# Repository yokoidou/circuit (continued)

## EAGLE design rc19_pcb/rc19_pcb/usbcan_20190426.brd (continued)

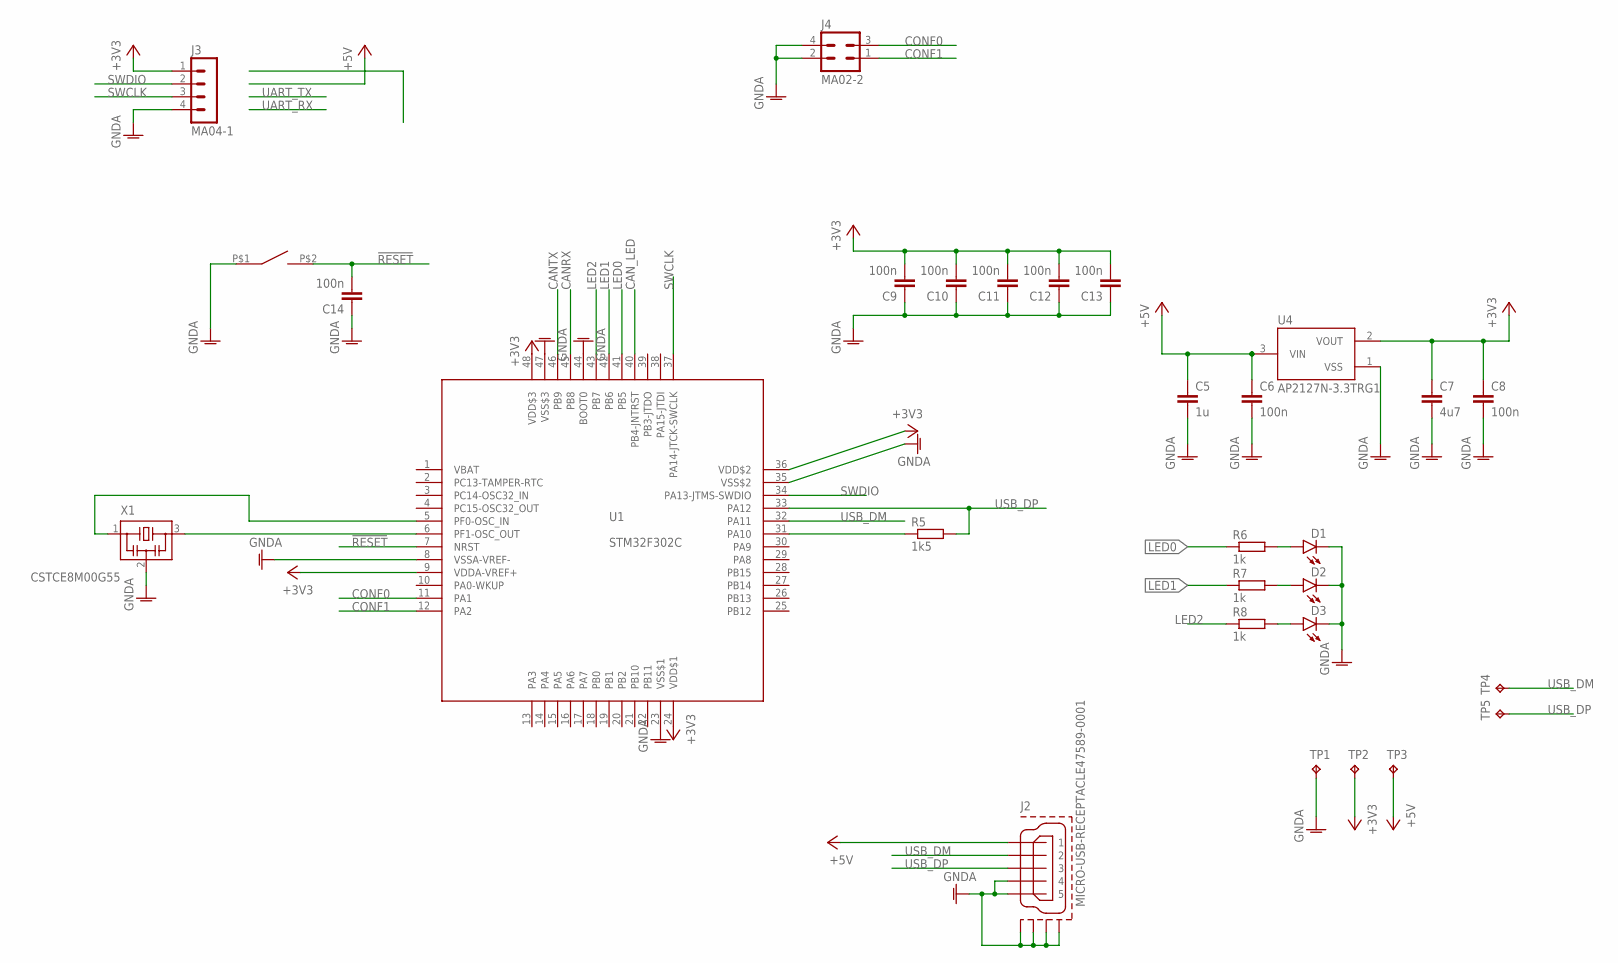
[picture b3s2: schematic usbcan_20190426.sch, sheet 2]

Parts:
C5: 1u; C0603
C6, C8, C9, C10, C11, C12, C13, C14: 100n; C0603
C7: 4u7; C0805
D1, D2, D3: LEDCHIPLED_0805; CHIPLED_0805
J2: MICRO-USB-RECEPTACLE47589-0001; 47589-0001
J3: MA04-1
J4: MA02-2; MA02-2W
R5: 1k5; R0603
R6, R7, R8: 1k; R0603
S1: SWITCH_TACTILETOP; SWITCH_TACTILE_3X6
TP1, TP2, TP3, TP4, TP5: TPB1,27; B1,27
U1: STM32F302C; LQFP48
U4: AP2127N-3.3TRG1; SOT95P240X110-3
X1: CSTCE8M00G55

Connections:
!RESET: C14.2, S1.P$2 (2), U1.7 (NRST)
+3V3: C7.1, C8.1, C9.2, C10.2, C11.2, C12.2, C13.2, J3.1, TP2.TP, U1.9 (VDDA-VREF+), U1.24 (VDD$1), U1.36 (VDD$2), U1.48 (VDD$3), U4.2 (VOUT); also elsewhere on the board
+5V: C5.1, C6.1, J2.1, TP3.TP, U4.3 (VIN)
CANRX: U1.45 (PB8); also elsewhere on the board
CANTX: U1.46 (PB9); also elsewhere on the board
CAN_LED: U1.40 (PB4-JNTRST); also elsewhere on the board
CONF0: J4.3, U1.11 (PA1)
CONF1: J4.1, U1.12 (PA2)
GNDA: C5.2, C6.2, C7.2, C8.2, C9.1, C10.1, C11.1, C12.1, C13.1, C14.1, D1.C, D2.C, D3.C, J2.4, J2.5, J2.CASING1 (GND1), J2.CASING2 (GND2), J2.CASING3 (GND3), J2.CASING4 (GND4), J2.P$1 (GND1), J2.P$2 (GND1), J2.P$3 (GND2), J2.P$4 (GND2), J3.4, J4.2, J4.4, S1.P$1 (1), TP1.TP, U1.8 (VSSA-VREF-), U1.23 (VSS$1), U1.35 (VSS$2), U1.44 (BOOT0), U1.47 (VSS$3), U4.1 (VSS), X1.2; also elsewhere on the board
LED0: R6.1, U1.41 (PB5)
LED1: R7.1, U1.42 (PB6)
LED2: R8.1, U1.43 (PB7)
unnamed: D2.A, R7.2
unnamed: D1.A, R6.2
unnamed: U1.6 (PF1-OSC_OUT), X1.3
unnamed: U1.5 (PF0-OSC_IN), X1.1
unnamed: R5.1, U1.31 (PA10)
unnamed: D3.A, R8.2
SWCLK: J3.3, U1.37 (PA14-JTCK-SWCLK)
SWDIO: J3.2, U1.34 (PA13-JTMS-SWDIO)
USB_DM: J2.2, TP4.TP, U1.32 (PA11)
USB_DP: J2.3, R5.2, TP5.TP, U1.33 (PA12)

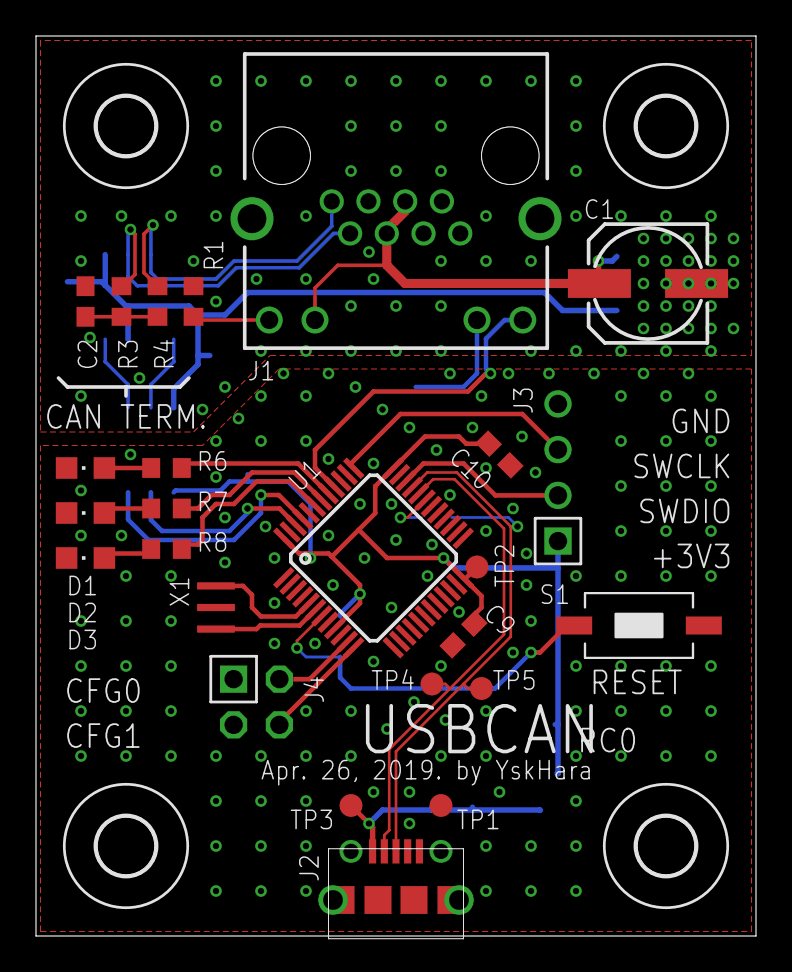
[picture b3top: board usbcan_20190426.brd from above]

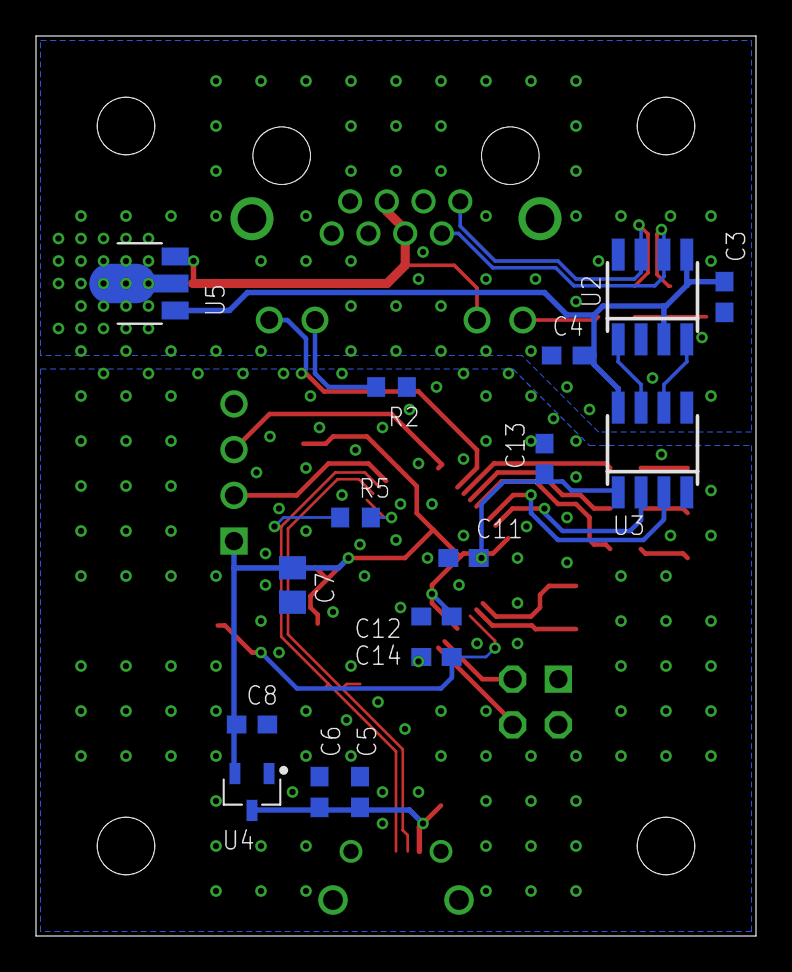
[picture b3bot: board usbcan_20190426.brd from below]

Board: 2 copper layers, 40.0 x 50.0 mm, 45 parts (16 on the bottom side), 32 nets.

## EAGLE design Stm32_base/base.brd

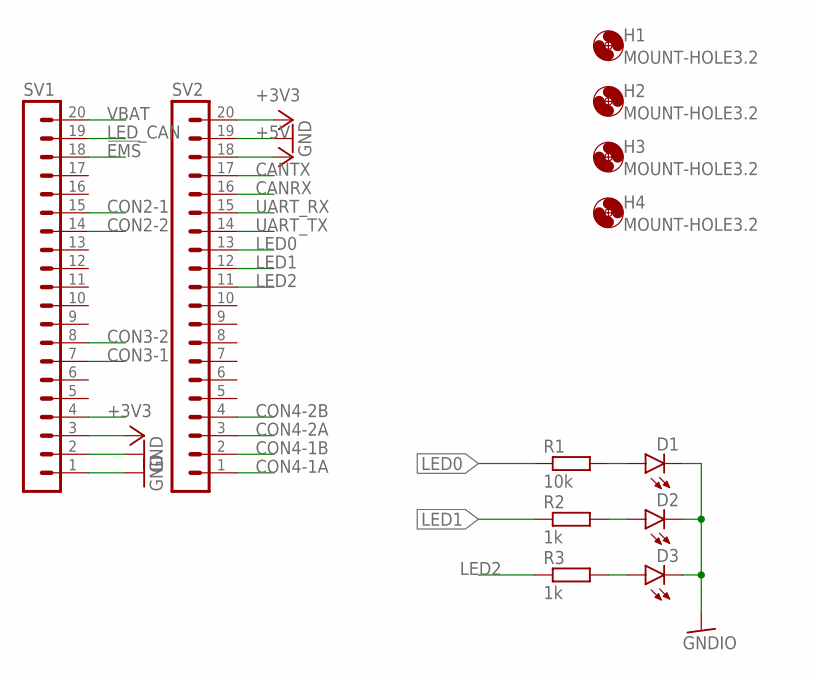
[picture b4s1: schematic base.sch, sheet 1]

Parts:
D1, D2, D3: LEDCHIPLED_0805; CHIPLED_0805
H1, H2, H3, H4: MOUNT-HOLE3.2; 3,2
R1: 10k; R0603
R2, R3: 1k; R0603
SV1, SV2: MA20-1L

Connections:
!EMS: SV1.18; also elsewhere on the board
+3V3: SV1.3, SV2.20; also elsewhere on the board
+5V: SV2.18; also elsewhere on the board
CANRX: SV2.16; also elsewhere on the board
CANTX: SV2.17; also elsewhere on the board
CON2-1: SV1.15; also elsewhere on the board
CON2-2: SV1.14; also elsewhere on the board
CON3-1: SV1.7; also elsewhere on the board
CON3-2: SV1.8; also elsewhere on the board
CON4-1A: SV2.1; also elsewhere on the board
CON4-1B: SV2.2; also elsewhere on the board
CON4-2A: SV2.3; also elsewhere on the board
CON4-2B: SV2.4; also elsewhere on the board
GND: D1.C, D2.C, D3.C, SV1.1, SV1.2, SV2.19; also elsewhere on the board
LED0: R1.1, SV2.13
LED1: R2.1, SV2.12
LED2: R3.1, SV2.11
LED_CAN: SV1.19; also elsewhere on the board
unnamed: D2.A, R2.2
unnamed: D1.A, R1.2
unnamed: D3.A, R3.2
UART_RX: SV2.15
UART_TX: SV2.14
VBAT: SV1.20

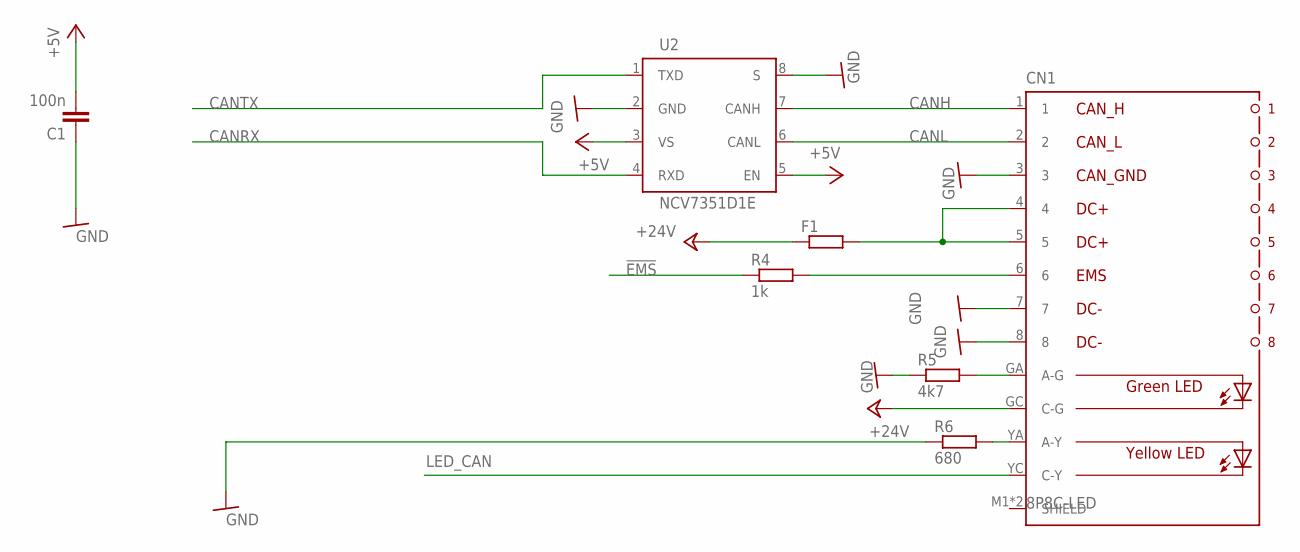
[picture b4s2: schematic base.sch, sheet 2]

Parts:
C1: 100n; C0603
CN1: 8P8C-LED
F1: R-EU_R1206; R1206
R4: 1k; R0603
R5: 4k7; R0603
R6: 680; R0603
U2: NCV7351D1E; SO08

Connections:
!EMS: R4.1; also elsewhere on the board
!EMS_ISO: CN1.6, R4.2
+5V: C1.2, U2.3 (VS), U2.5 (EN); also elsewhere on the board
+24V: CN1.GC (C-G), F1.1; also elsewhere on the board
CANH: CN1.1, U2.7 (CANH)
CANL: CN1.2, U2.6 (CANL)
CANRX: U2.4 (RXD); also elsewhere on the board
CANTX: U2.1 (TXD); also elsewhere on the board
GND: C1.1, CN1.3, CN1.7, CN1.8, R5.1, R6.1, U2.2 (GND), U2.8 (S); also elsewhere on the board
LED_CAN: CN1.YC (C-Y); also elsewhere on the board
unnamed: CN1.GA (A-G), R5.2
unnamed: CN1.YA (A-Y), R6.2
unnamed: CN1.4, CN1.5, F1.2

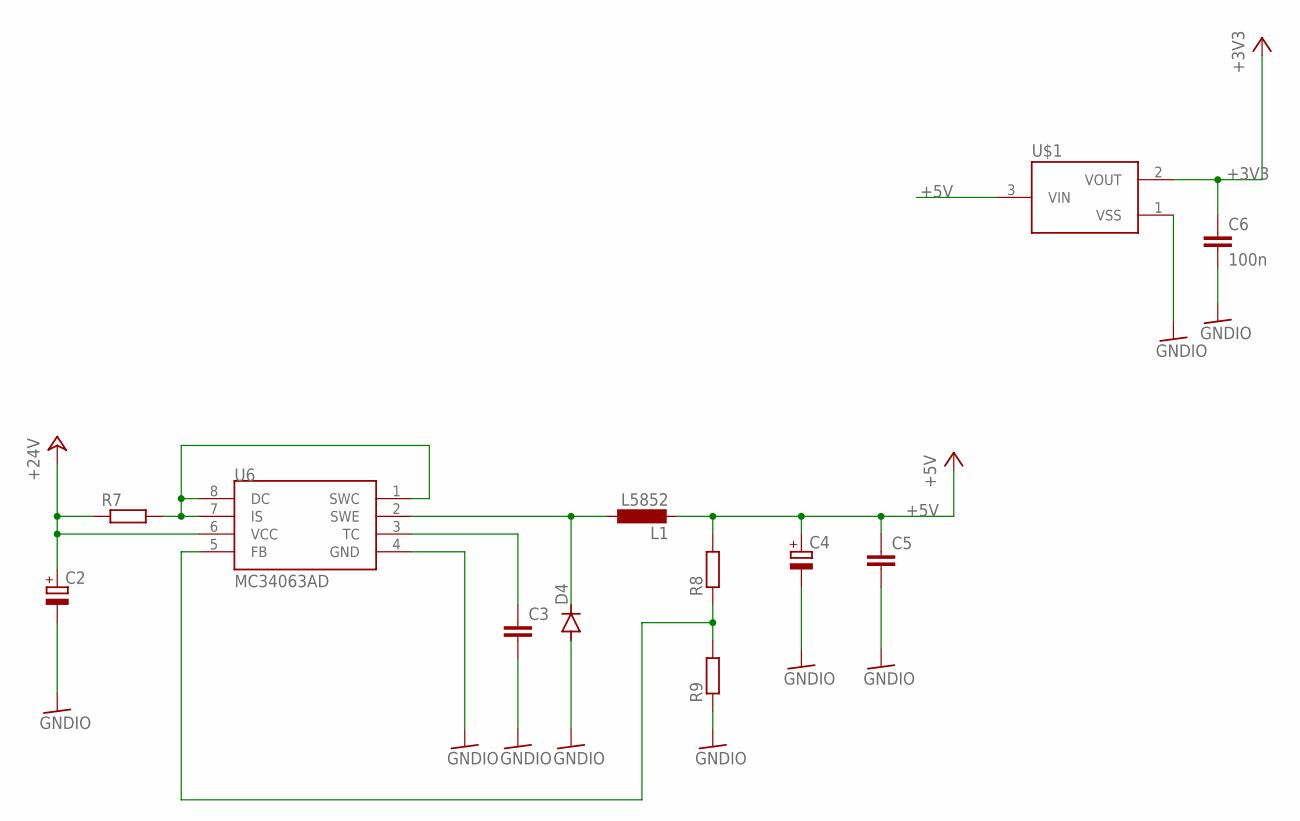
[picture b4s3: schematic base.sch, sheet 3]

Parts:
C2, C4: CPOL-EUE2-5; E2-5
C3, C5: C-EUC0603; C0603
C6: 100n; C0603
D4: DIODE-SOD123; SOD123
L1: L5852
R7: R-EU_R1206; R1206
R8, R9: R-EU_R0603; R0603
U6: MC34063AD; SOIC8
U$1: XC6206; SOT95P240X110-3

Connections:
+3V3: C6.1, U$1.2 (VOUT); also elsewhere on the board
+5V: C4.+, C5.1, L1.P$2 (2), R8.2, U$1.3 (VIN); also elsewhere on the board
+24V: C2.+, R7.1, U6.6 (VCC); also elsewhere on the board
GND: C2.-, C3.2, C4.-, C5.2, C6.2, D4.A, R9.1, U6.4 (GND), U$1.1 (VSS); also elsewhere on the board
unnamed: R7.2, U6.1 (SWC), U6.7 (IS), U6.8 (DC)
unnamed: D4.C, L1.P$1 (1), U6.2 (SWE)
unnamed: C3.1, U6.3 (TC)
unnamed: R8.1, R9.2, U6.5 (FB)

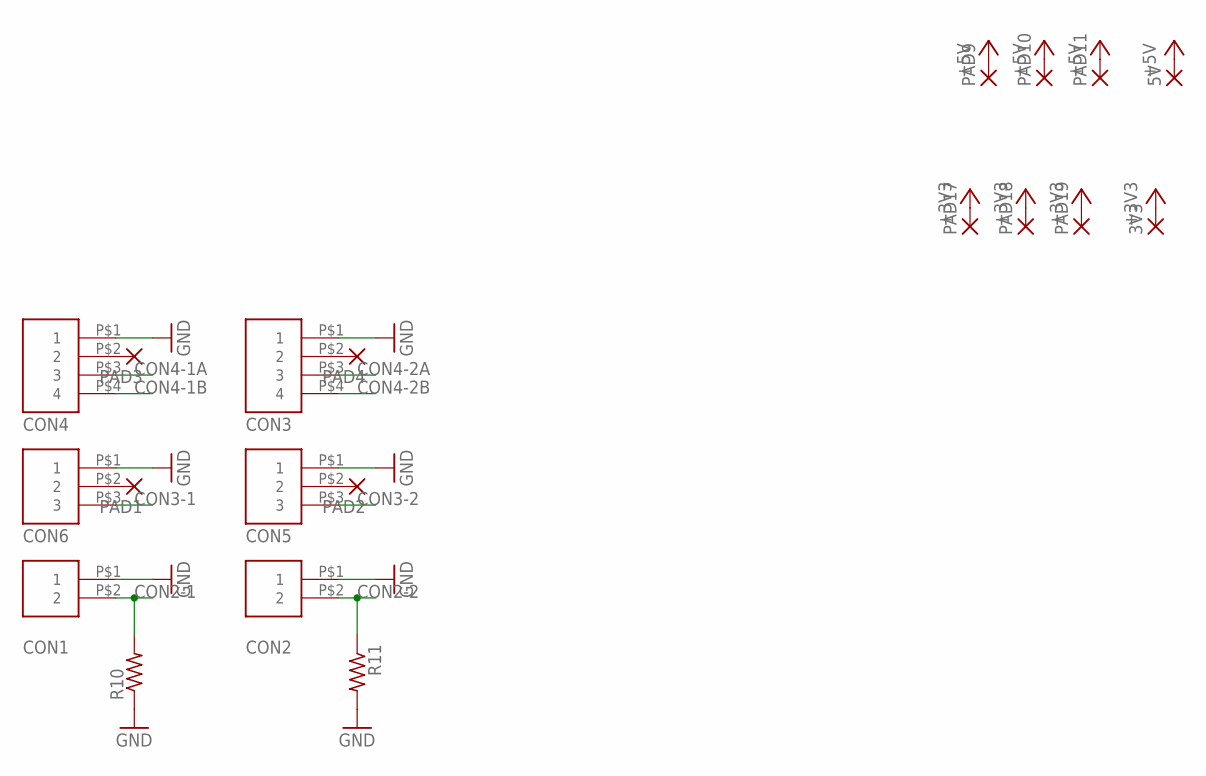
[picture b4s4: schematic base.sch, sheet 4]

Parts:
3V3, 5V: SMD2; SMD1,27-2,54
CON1, CON2: XH-2-SIDE; CON-XH-2-SIDE
CON3, CON4: XH-4-SIDE; CON-XH-4-SIDE
CON5, CON6: XH-3-SIDE; CON-XH-3-SIDE
PAD1, PAD2, PAD3, PAD4, PAD9, PAD10, PAD11, PAD17, PAD18, PAD19: SMD2; SMD1,27-2,54
R10, R11: R-US_R0603; R0603

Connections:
+3V3: 3V3.1, PAD17.1, PAD18.1, PAD19.1; also elsewhere on the board
+5V: 5V.1, PAD9.1, PAD10.1, PAD11.1; also elsewhere on the board
CON2-1: CON1.P$2 (2), R10.2; also elsewhere on the board
CON2-2: CON2.P$2 (2), R11.1; also elsewhere on the board
CON3-1: CON6.P$3 (3); also elsewhere on the board
CON3-2: CON5.P$3 (3); also elsewhere on the board
CON4-1A: CON4.P$3 (3); also elsewhere on the board
CON4-1B: CON4.P$4 (4); also elsewhere on the board
CON4-2A: CON3.P$3 (3); also elsewhere on the board
CON4-2B: CON3.P$4 (4); also elsewhere on the board
GND: CON1.P$1 (1), CON2.P$1 (1), CON3.P$1 (1), CON4.P$1 (1), CON5.P$1 (1), CON6.P$1 (1), R10.1, R11.2; also elsewhere on the board
unnamed: CON3.P$2 (2), PAD4.1
unnamed: CON5.P$2 (2), PAD2.1
unnamed: CON4.P$2 (2), PAD3.1
unnamed: CON6.P$2 (2), PAD1.1

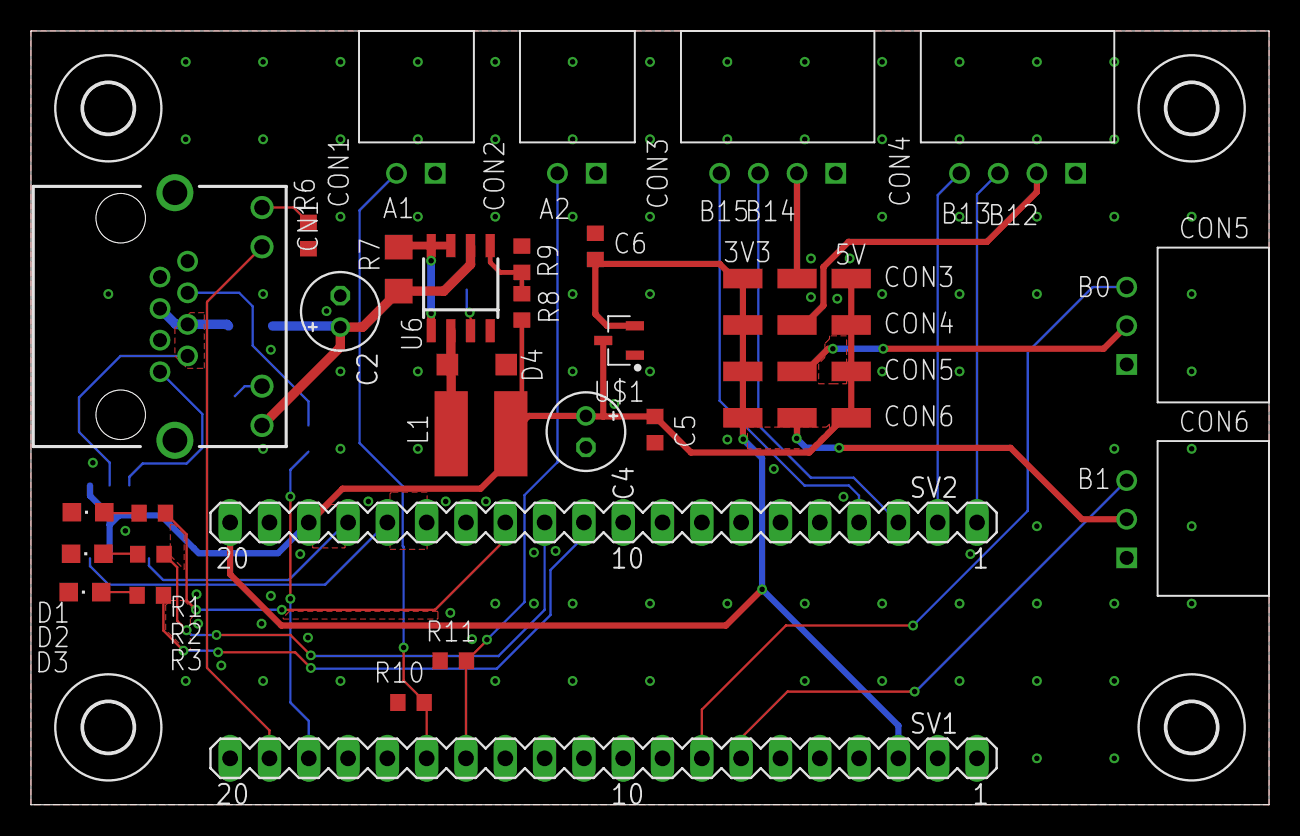
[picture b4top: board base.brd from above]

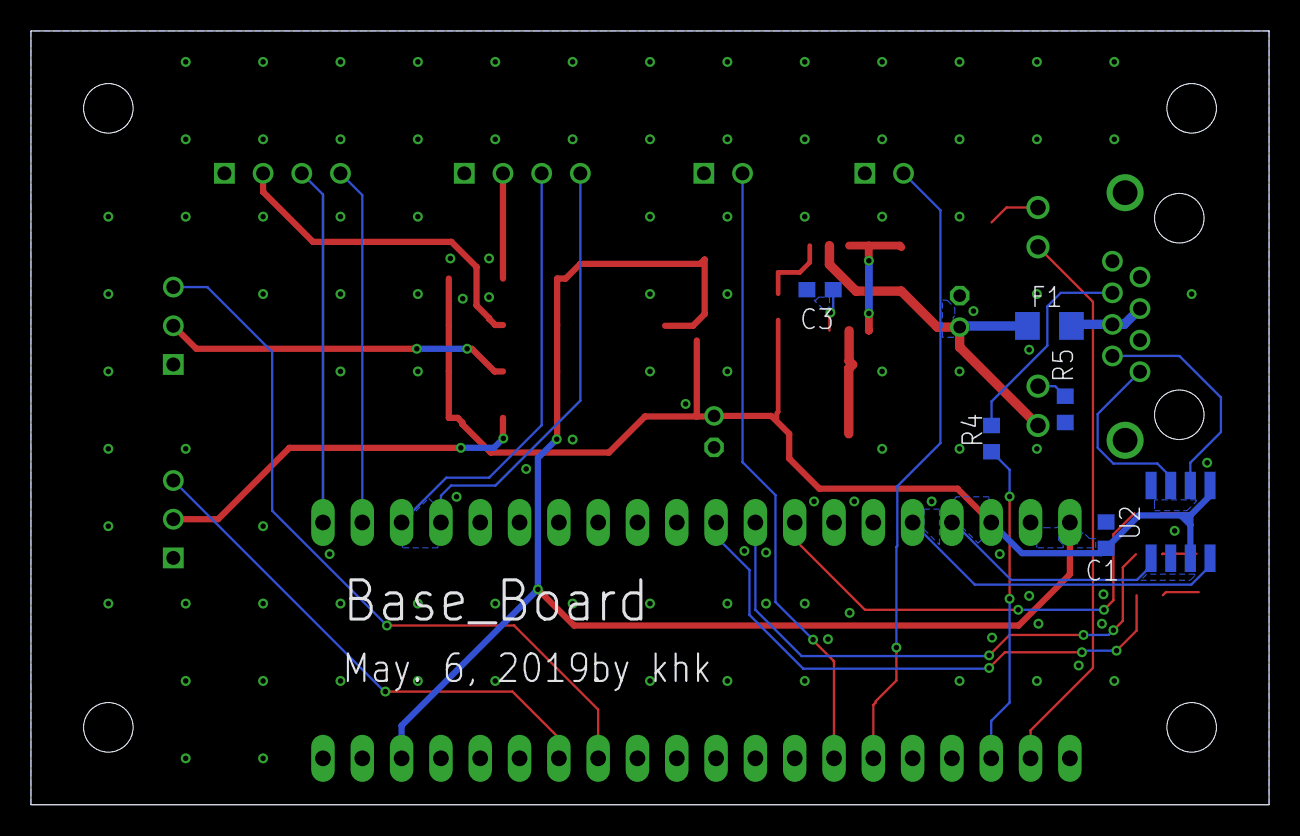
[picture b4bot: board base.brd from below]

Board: 2 copper layers, 80.0 x 50.0 mm, 51 parts (6 on the bottom side), 36 nets.

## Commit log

2019-06-17 Create boards
2019-06-19 Rename Readme to README.md
2019-06-26 Add files via upload
    コネクタ色々付いててCAN通信できてf1のボード乗っけるよくわからん基板
2019-06-29 Add files via upload
    USBCANのBOOT0がGNDに接地していないミスを修正
2019-07-20 Create switching
